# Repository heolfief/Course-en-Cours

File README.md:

<p align="center">

<h1 align="center">Course en cours</h1>

<p align="center">
	<a target="_blank" href="http://www.course-en-cours.com/">www.course-en-cours.com</a>
</p>
</p>
<HR>
<br>

<p align="center">
	
	<a target="_blank" href="https://github.com/heolfief/Course-en-Cours/blob/master/README_FR.md">VERSION EN FRANCAIS / FRENCH VERSION</a>
</p>

## Table of contents

- [Description](#description)
- [Where to start](#where-to-start)
- [Hardware](#hardware)
- [Software](#software)
- [Creators](#creators)
- [Copyright and license](#copyright-and-license)

## Description

This project contains hardware, software and documentation files for the "course en cours" **educationnal competition in France**.
During a year, teams of 4 to 6 middle/high school **students build their small electic car** using the same tools as engineers. the contest consists of **designing, creating, testing and running** a small model car during the **regional competitions**, to acces the **national final**.

We are two university students in electrical engineering and industrial data processing, from <a href="https://iut-rennes.univ-rennes1.fr/les-6-departements/genie-electrique-informatique-industrielle">IUT de Rennes</a>, France.
Our project is to **integrate embedded telemetry, datalogging and manual control** into the existings cars engines.
We choosed to works with the **Arduino environnement**, to make it possible for everybody to program their car, modify it as they like, and to make programming accesible for the young people of the competition.

This project is **realesed under the general public license and is strongly welcome to modifications**.

## Where to start

In order to be able to program your board with the arduino IDE via usb, you will first need to install a bootloader on your board. Find insruction on how to do that in the <a href="#bootloader">software section</a>.

When this step is done you should be able to programm your board like if it was an arduinon pro mini.

Just install the course-en-cours library (<a href="#software">link in the software section</a>) and import it to your arduino sketch.
<a target="_blank" href="https://www.arduino.cc/en/Guide/Libraries">Here is a tutorial</a> if you need help for this step.

You should now be able to program your board via USB, as described in the <a href="#software">software section</a>.

## Hardware

The hardware is based on 4 main components:
- ATmega328p microcontroller (the same as the arduino uno/nano/pro mini)
- MPU6050 accelerometer and gyro chip
- A FTDI chip (to program the microcontroller via USB)
- A micro SD card holder

This board is **fully arduino compatible** and should be selected in the arduino environnement as the arduino pro mini (ATmega328p, 3.3V 8MHz).

### Documents availables

- <a target="_blank" href="https://github.com/heolfief/Course-en-Cours/blob/master/Hardware/Schematics.pdf">Schematics (PDF)</a>
- <a target="_blank" href="https://github.com/heolfief/Course-en-Cours/blob/master/Hardware/BOM.pdf">Bill of materials (PDF)</a>
- <a target="_blank" href="https://github.com/heolfief/Course-en-Cours/blob/master/Hardware/Carte%20course%20en%20cours.sch">Autodesk Eagle schematics file</a>
- <a target="_blank" href="https://github.com/heolfief/Course-en-Cours/blob/master/Hardware/Carte%20course%20en%20cours.brd">Autodesk Eagle board file</a>
- <a href="https://github.com/heolfief/Course-en-Cours/blob/master/Hardware/Gerbers.zip">Gerber files</a>

### Board form factor
<table border="0">
	<tbody>
		<tr>
			<th align="center"></th>
			<th align="center"></th>
		</tr>
	</tbody>
</table>

### PCB pinout diagram:

### PCB wiring diagram:

**BE CAREFULL: You need to provide 3.3V to the board, plugging directly the 11.1V LiPo battery will kill it. You can step down the battery voltage with a standard DC/DC converter (also known as buck-converter) set to output 3.3V (min 200mA), like in the wiring diagram above.**

## Software

### Firmware

You can program your course en cours board in C/C++ directly with the <a target="_blank" href="https://www.arduino.cc/en/main/software">arduino IDE</a> via USB, assuming you already have a bootloader installed on your board. Instructions on how to flash a bootloader <a href="#bootloader">below</a>.

In the arduino IDE, select the "arduino pro mini" under Tools/Board, and the ATmega328p 3.3V 8MHz under Tools/Processor. Then select the COM port (under Tools/Port) on wich the board is plugged.
To access all the course en cours related function, just import the "course_en_cours" library to your sketch.
<a target="_blank" href="https://www.arduino.cc/en/Guide/Libraries">Here is a tutorial</a> if you need help for this step.

You should now be able to program your board with the arduino software environement.

The delay() function from the Arduino IDE shouldn't be used in your program because it will block the process of our library.

#### Needed libraries

- [MPU6050](https://github.com/jarzebski/Arduino-MPU6050) by **_jarzebski_** : Allows us to use the IMU.
- [SDFat](https://github.com/greiman/SdFat) by **_greiman_** : Allows us to get a high speed SD card communication.

#### Exemple code:
```cpp
#include "Course_en_Cours.h"

Couse_en_Cours cec;	 // create Couse_en_Cours object

void setup() {
	cec.initialiser(AUTO);
	cec.palier_moteur(1000,0);
	cec.palier_moteur(5000,50);
	cec.palier_moteur(7500,75);
}

void loop() {
	cec.executer();
}
```
<table>
	<tbody>
		<tr>
			<th align="center">Function</th>
			<th align="center">Description</th>
			<th align="center">Parameters</th>
		</tr>
		<tr>
			<td><code>cec.executer(void);</code></td>
			<td>Mandatory function, needs to be run in the loop().</td>
			<td>
				<ul>
				<li><strong>cec</strong> : a variable of type Course_en_cours</li>
				</ul>
			</td>
		</tr>
		<tr>
			<td><code>cec.initialiser(bool pilotage_mode);</code></td>
			<td>Function to set the driving mode. Needs to be run in the setup().</td>
			<td>
				<ul>
				<li><strong>cec</strong> : a variable of type Course_en_cours</li>
				<li><strong>pilotage_mode</strong> : the mode you want your car to run in. Can be set to "AUTO" or "MANU".
					<ul>
						<li>AUTO : you can drive the motor within your arduino code with the palier_moteur function.</li>
						<li>MANU : palier_moteur functions are disabled, and remote control signal is redirected to the ESC. You can manualy drive the motors with a remote.</li>
					</ul>
				</li>
				</ul>
			</td>
		</tr>
		<tr>
			<td><code>cec.palier_moteur(unsigned int ms, unsigned char pourcentage);</code></td>
			<td>The motor power step function. Use it in the setup() to set a fixed power/speed to the motor at a certain time. Can be called several times to create differents steps at different times. </td>
			<td>
				<ul>
					<li><strong>cec</strong> : a variable of type Course_en_cours</li>
					<li><strong>ms</strong> : the time in milieconds you want the function to take effect. Timer starts right after power-up.</li>
					<li><strong>pourcentage</strong> : this sets the power/speed of the motor, in percentage.</li>
				</ul>
			</td>
		</tr>
	</tbody>
</table>

#### Known issues

The actual software have some issues :
- If the .csv file is not already on the SD card, the logging would be slower than expected. Make sure that the file already exists on the card.
- The logging time may vary depending of how many steps (palier_moteur functions) you have added.
- The object Course_en_Cours must be called "cec" and declared as global variable (away from the loop() and setup(), or from any fonction).

### Bootloader

In order to be able to program your board with the arduino IDE via usb, you will first need to install a bootloader on your board. Sparkfun have made an easy to understand tutorial on how to do that here : <a target="_blank" href="https://learn.sparkfun.com/tutorials/installing-an-arduino-bootloader">Installing an arduino bootloader</a>

Here is the wiring diagram to install the bootloader with an arduino UNO (follow the sparkfun tutorial for step by step instructions).

When installing the bootloader, make sure your arduino target board is the arduino pro mini (ATmega328p 3.3V 8MHz), as this board is arduino pro mini compatible.

You should now be able to program your board via USB, as described in the <a href="#software">software section</a>.

## Creators

**Heol Fief**

- <https://github.com/heolfief>

**Dylan Gageot**

- <https://github.com/dylangageot>

## Copyright and license
heolfief/Course-en-Cours is licensed under the GNU General Public License v3.0.

See the <a target="_blank" href="https://github.com/heolfief/Course-en-Cours/blob/master/LICENSE">LICENSE file</a> for more informations.

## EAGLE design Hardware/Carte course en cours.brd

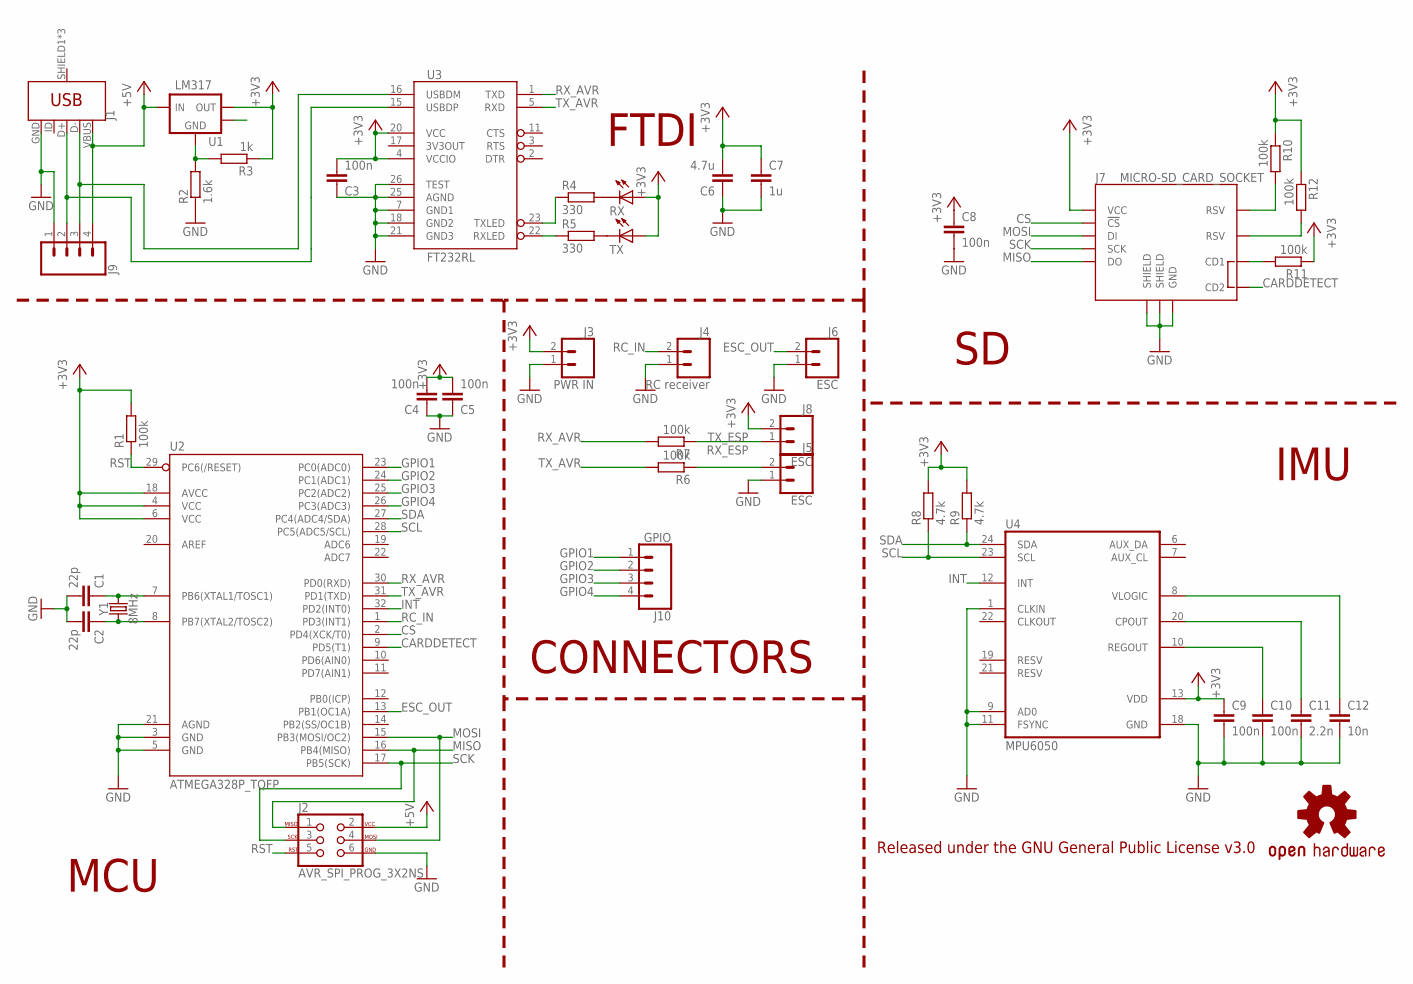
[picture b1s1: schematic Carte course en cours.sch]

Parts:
C1, C2: 22p; C0805
C3, C4, C5, C8, C9, C10: 100n; C0805
C6: 4.7u; C0805
C7: 1u; C0805
C11: 2.2n; C0805
C12: 10n; C0805
J1: USB_MICRO-B_FEMALE-SMT; USB-B-MICRO-SMD
J2: AVR_SPI_PROG_3X2NS; 2X3-NS
J3: PWR IN; 1X02
J4: RC receiver; 1X02
J5, J6, J8: ESC; 1X02
J7: MICRO-SD_CARD_SOCKET; MICRO-SD-SOCKET
J9: CONN_04; 1X04
J10: GPIO; 1X04
LOGO1: OSHW-LOGOM; OSHW-LOGO-M
R1, R6, R7, R10, R11, R12: 100k; R0805
R2: 1.6k; R0805
R3: 1k; R0805
R4, R5: 330; R0805
R8, R9: 4.7k; R0805
RX: LEDCHIPLED_0805; CHIPLED_0805
TX: LEDCHIPLED_0805; CHIPLED_0805
U1: LM317; SOT-223-3
U2: ATMEGA328P_TQFP; TQFP32-08
U3: FT232RL; SSOP28DB
U4: MPU6050; HVQFN24_NS
Y1: 8MHz; CRYSTAL-SMD-5X3.2-4PAD

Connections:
+3V3: C3.2, C4.2, C5.2, C6.2, C7.1, C8.1, C9.1, J3.2, J7.VCC, J8.2, R1.2, R3.1, R8.2, R9.2, R10.1, R11.1, R12.1, RX.A, TX.A, U1.2 (VOUT), U2.4 (VCC), U2.6 (VCC), U2.18 (AVCC), U3.4 (VCCIO), U3.20 (VCC), U4.13 (VDD)
+5V: J1.VBUS, J2.2, J9.4, U1.3 (VIN)
CARDDETECT: J7.CD2, U2.9 (PD5(T1))
CS: J7.CS (!CS), U2.2 (PD4(XCK/T0))
ESC_OUT: J6.2, U2.13 (PB1(OC1A))
GND: C1.2, C2.2, C3.1, C4.1, C5.1, C6.1, C7.2, C8.2, C9.2, C10.2, C11.2, C12.2, J1.GND, J2.6, J3.1, J4.1, J5.1, J6.1, J7.GND, J7.GND1 (SHIELD), J7.GND3 (SHIELD), J9.1, R2.1, U2.3 (GND), U2.5 (GND), U2.21 (AGND), U3.7 (GND1), U3.18 (GND2), U3.21 (GND3), U3.25 (AGND), U3.26 (TEST), U4.1 (CLKIN), U4.9 (AD0), U4.11 (FSYNC), U4.18 (GND)
GPIO1: J10.1, U2.23 (PC0(ADC0))
GPIO2: J10.2, U2.24 (PC1(ADC1))
GPIO3: J10.3, U2.25 (PC2(ADC2))
GPIO4: J10.4, U2.26 (PC3(ADC3))
HEATSINK: U1.4 (HEATSINK)
INT: U2.32 (PD2(INT0)), U4.12 (INT)
MISO: J2.1, J7.DO, U2.16 (PB4(MISO))
MOSI: J2.4, J7.DI, U2.15 (PB3(MOSI/OC2))
unnamed: R2.2, R3.2, U1.1 (GND)
unnamed: J1.D-, J9.3, U3.16 (USBDM)
unnamed: C1.1, U2.7 (PB6(XTAL1/TOSC1)), Y1.3 (2)
unnamed: C2.1, U2.8 (PB7(XTAL2/TOSC2)), Y1.1
unnamed: J1.D+, J9.2, U3.15 (USBDP)
unnamed: C11.1, U4.20 (CPOUT)
unnamed: R4.1, U3.23 (TXLED)
unnamed: R5.1, U3.22 (RXLED)
unnamed: R4.2, RX.C
unnamed: R5.2, TX.C
unnamed: C10.1, U4.10 (REGOUT)
unnamed: C12.1, U4.8 (VLOGIC)
unnamed: J7.RSV1 (RSV), R10.2
unnamed: J7.RSV2 (RSV), R12.2
unnamed: J7.CD1, R11.2
RC_IN: J4.2, U2.1 (PD3(INT1))
RST: J2.5, R1.1, U2.29 (PC6(/RESET))
RX_AVR: R7.2, U2.30 (PD0(RXD)), U3.1 (TXD)
RX_ESP: J5.2, R6.1
SCK: J2.3, J7.SCLK (SCK), U2.17 (PB5(SCK))
SCL: R8.1, U2.28 (PC5(ADC5/SCL)), U4.23 (SCL)
SDA: R9.1, U2.27 (PC4(ADC4/SDA)), U4.24 (SDA)
TX_AVR: R6.2, U2.31 (PD1(TXD)), U3.5 (RXD)
TX_ESP: J8.1, R7.1

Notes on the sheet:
MCU
IMU
FTDI
Released under the GNU General Public License v3.0
CONNECTORS

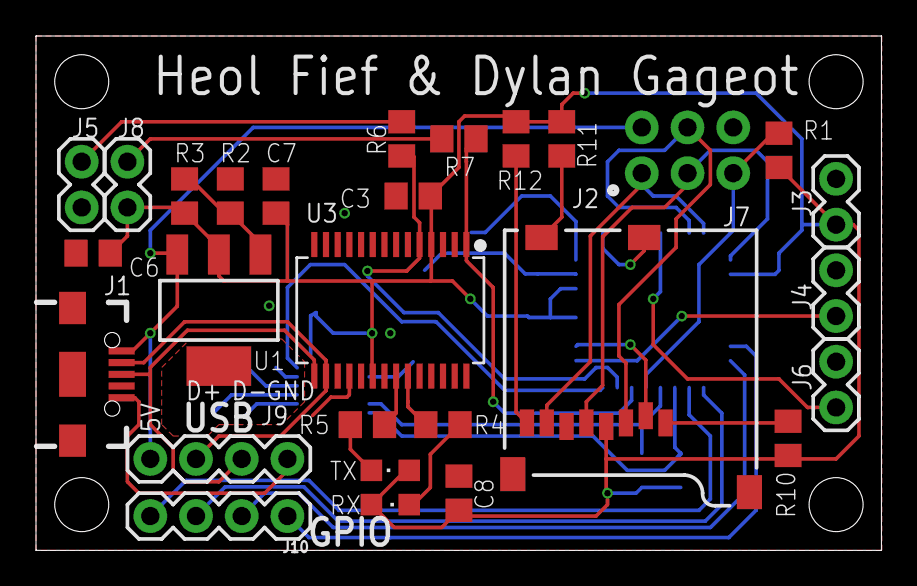
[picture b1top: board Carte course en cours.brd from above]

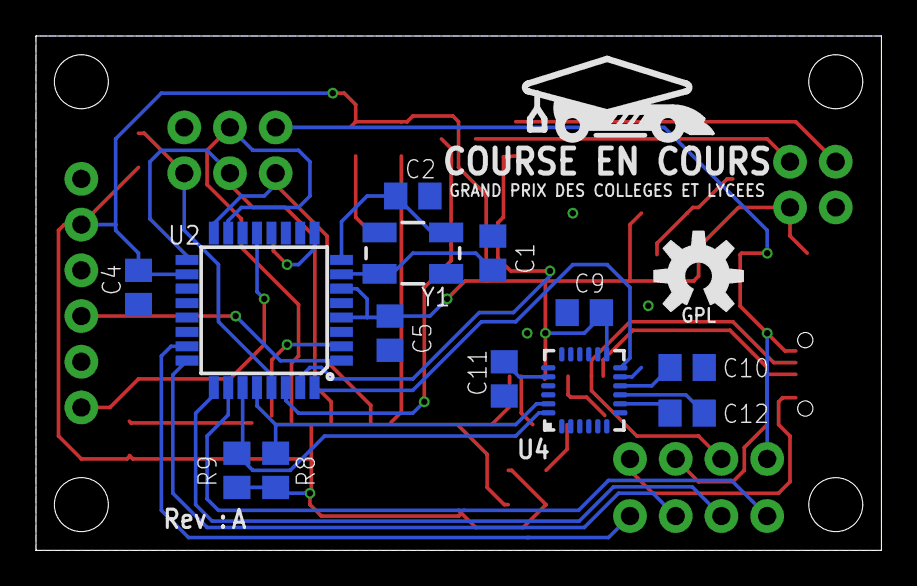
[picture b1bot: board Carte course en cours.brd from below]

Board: 2 copper layers, 47.0 x 28.6 mm, 42 parts (14 on the bottom side), 37 nets.

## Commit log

2017-11-30 Add Schematics files
2017-11-30 Add event website
2017-12-02 Add connectors
2017-12-02 Add brd file
2017-12-05 Place components
2017-12-05 Routing
2017-12-06 Add gitignore
2017-12-06 update gitignore
2017-12-06 Add project file
2017-12-06 Update project file
2017-12-07 Route
2017-12-09 Add silkscreen
2017-12-09 Add schematics PDF
2017-12-09 Add BOM
2017-12-09 Add price to BOM
2017-12-09 Improce pwr trace lenght
2017-12-10 Add heatsink plane
2017-12-15 Improve trace shape
2017-12-15 Add pinout diagram
2017-12-15 Remove space in file name
2017-12-15 Add project description
2017-12-15 Add hearders
2017-12-15 remove eagle.epf file
2017-12-15 remove libreoffice file
2017-12-15 Add course en cours logo
2017-12-16 align logo
2017-12-16 Add html hr tag
2017-12-16 Add table of content
2017-12-16 Add creators and license
2017-12-16 Add header
2017-12-16 Add hardware files links
2017-12-16 Add quick start guide
2017-12-16 Add links
2017-12-16 Update link
2017-12-16 Add fritzing schematics
2017-12-16 Add wiring diagrams
2017-12-16 Add ESC and RC receiver
2017-12-16 Add ESC and RC receiver to wiring diagram
2017-12-16 Add max voltage warning
2017-12-16 Add ISP pin 1 indentifier
2017-12-17 Update wiring diagrams
2017-12-17 Fix md bold format
2017-12-17 Fix images aspect ratio
2017-12-17 Update software section
2017-12-17 Add new tab option to links
2017-12-17 Add missing link
2017-12-19 Add french version link
2017-12-19 Create newfolder
2017-12-21 Update Course_en_Cours.h and .cpp
    The library can be build with the Arduino IDE compiler -> need to test this library on the prototype.
2017-12-23 Update library
2017-12-31 Remove sticky notes
2017-12-31 Add doc files
2018-01-09 Create test
2018-01-09 Rename Documentation/files/test to Resources/newfolder
2018-01-09 Update the datalogging timing
2018-01-09 Modify images URL
2018-01-14 Add Gerbers
2018-02-04 Changed MCU frequency to 8MHz, to run safe at 3.3V
2018-03-28 Add 4 GPIO
2018-03-28 Add GPIO
2018-11-06 [ImgBot] Optimize images
    *Total -- 1,442.77kb -> 1,224.88kb (15.1%)
    /Resources/PCB_pinout.jpg -- 932.86kb -> 729.86kb (21.76%)
    /Resources/Bootloader.png -- 117.26kb -> 102.45kb (12.63%)
    /Resources/echelle.png -- 392.65kb -> 392.57kb (0.02%)

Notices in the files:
Hardware/Carte course en cours.brd:
GPL
parts and their libraries:
SparkFun-IC-Microcontroller: Licensing: Creative Commons ShareAlike 4.0 International - https://creativecommons.org/licenses/by-sa/4.0
